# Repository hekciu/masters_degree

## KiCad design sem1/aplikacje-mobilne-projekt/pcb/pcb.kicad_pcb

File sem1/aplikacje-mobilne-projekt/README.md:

## Building mobile app:
### If first time on new machine use this script: https://github.com/hekciu/leds/blob/master/mobile/init.sh
- sudo ./generate_keys.sh # once
- cp mobile/com/tanker/Secrets.java.template mobile/com/tanker/Secrets.java
#### Fill Secrets.java with esp32 mac address
### Later:
- sudo ./build.sh
- ./run.sh
- ./monitor.sh

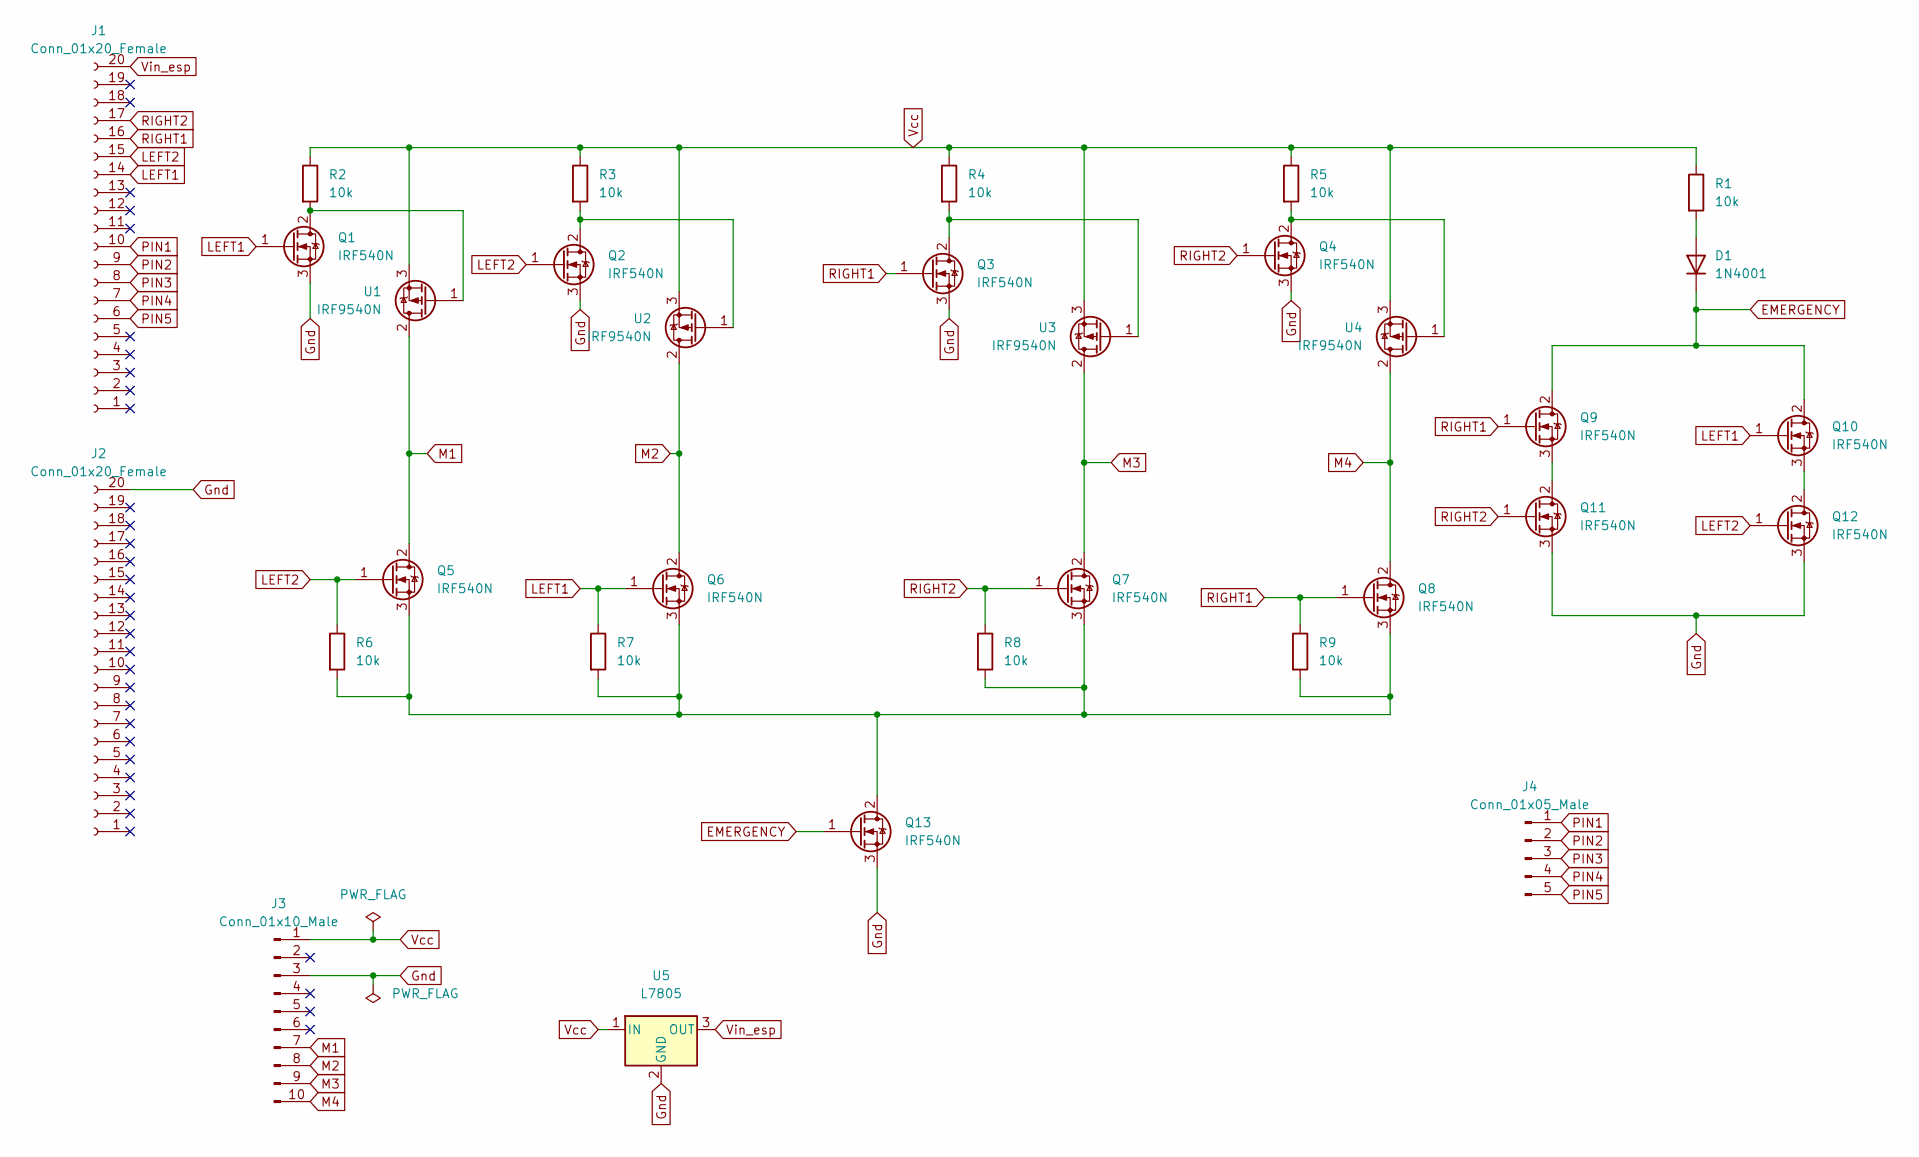
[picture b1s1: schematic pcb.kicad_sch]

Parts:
D1: 1N4001; D_DO-41_SOD81_P10.16mm_Horizontal
J1, J2: Conn_01x20_Female; PinHeader_1x20_P2.54mm_Vertical
J3: Conn_01x10_Male; PinHeader_1x10_P2.54mm_Vertical
J4: Conn_01x05_Male; PinHeader_1x05_P2.54mm_Vertical
Q1, Q2, Q3, Q4, Q5, Q6, Q7, Q8, Q9, Q10, Q11, Q12, Q13: IRF540N; TO-220-3_Vertical
R1, R2, R3, R4, R5, R6, R7, R8, R9: 10k; R_Axial_DIN0204_L3.6mm_D1.6mm_P7.62mm_Horizontal
U1, U2, U3, U4: IRF9540N; TO-220-3_Vertical
U5: L7805; TO-220-3_Vertical

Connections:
EMERGENCY: D1.1 (K), Q9.2 (D), Q10.2 (D), Q13.1 (G)
Gnd: J2.20, J3.3, Q1.3 (S), Q2.3 (S), Q3.3 (S), Q4.3 (S), Q11.3 (S), Q12.3 (S), Q13.3 (S), U5.2 (GND)
LEFT1: J1.14, Q1.1 (G), Q6.1 (G), Q10.1 (G), R7.1
LEFT2: J1.15, Q2.1 (G), Q5.1 (G), Q12.1 (G), R6.1
M1: J3.7, Q5.2 (D), U1.2 (D)
M2: J3.8, Q6.2 (D), U2.2 (D)
M3: J3.9, Q7.2 (D), U3.2 (D)
M4: J3.10, Q8.2 (D), U4.2 (D)
unnamed: D1.2 (A), R1.2
unnamed: Q1.2 (D), R2.2, U1.1 (G)
unnamed: Q2.2 (D), R3.2, U2.1 (G)
unnamed: Q3.2 (D), R4.2, U3.1 (G)
unnamed: Q4.2 (D), R5.2, U4.1 (G)
unnamed: Q10.3 (S), Q12.2 (D)
unnamed: Q9.3 (S), Q11.2 (D)
unnamed: Q5.3 (S), Q6.3 (S), Q7.3 (S), Q8.3 (S), Q13.2 (D), R6.2, R7.2, R8.2, R9.2
PIN1: J1.10, J4.1
PIN2: J1.9, J4.2
PIN3: J1.8, J4.3
PIN4: J1.7, J4.4
PIN5: J1.6, J4.5
RIGHT1: J1.16, Q3.1 (G), Q8.1 (G), Q9.1 (G), R9.1
RIGHT2: J1.17, Q4.1 (G), Q7.1 (G), Q11.1 (G), R8.1
Vcc: J3.1, R1.1, R2.1, R3.1, R4.1, R5.1, U1.3 (S), U2.3 (S), U3.3 (S), U4.3 (S), U5.1 (IN)
Vin_esp: J1.20, U5.3 (OUT)

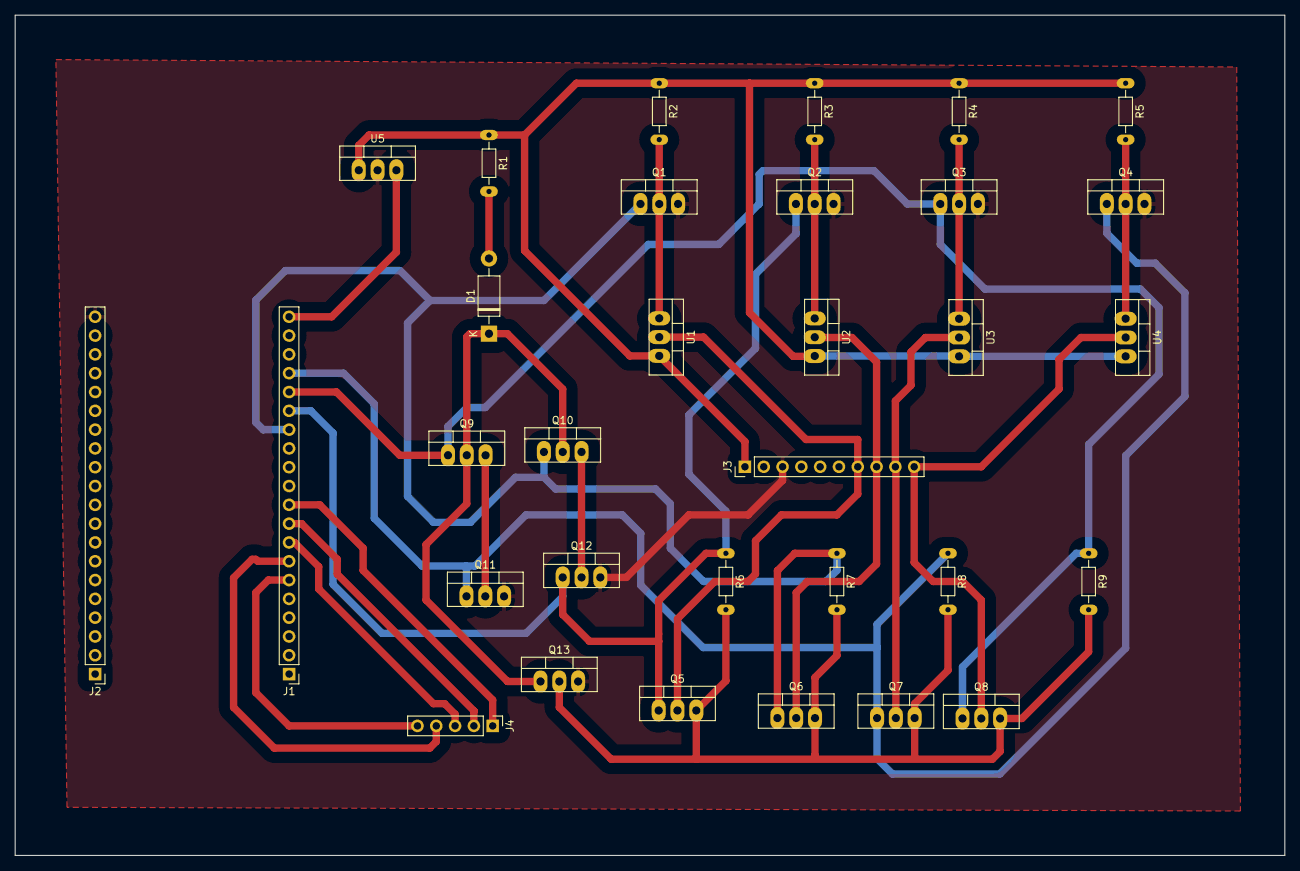
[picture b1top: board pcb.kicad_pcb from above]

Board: 2 copper layers, 171.5 x 113.5 mm, 32 parts (0 on the bottom side), 25 nets.

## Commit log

2024-11-14 init
2024-11-15 16.11.2024 systemy sterowania
2024-12-15 stuff
2024-12-28 mobile applications project
2024-12-28 Create LICENSE
2025-01-02 mobile apps tanker project mobile app
2025-01-03 init env for esp development
2025-01-03 copied most of the code from the leds project
2025-01-03 integrated app with esp
2025-01-08 electronic schematic draft apki mobilne
2025-01-11 aplikacje mobilne kicad schematic
2025-01-11 pcb schematic update
2025-01-12 apki mobilne finished software and updated kicad schematic
2025-01-12 kicad schematic
2025-01-16 update aplikacje mobilne schematic
2025-01-18 pcb update
2025-01-18 pcb design update
2025-01-19 this pcb one actually works
2025-01-22 PCB near end
